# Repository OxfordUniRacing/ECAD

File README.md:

View this project on [CADLAB.io](https://cadlab.io/project/1514). 

# ECAD
Schematics and designs for the electronics team
See notes on project struture in the Oxford Uni Racing ECAD project description.
Built with EAGLE 9.2.2

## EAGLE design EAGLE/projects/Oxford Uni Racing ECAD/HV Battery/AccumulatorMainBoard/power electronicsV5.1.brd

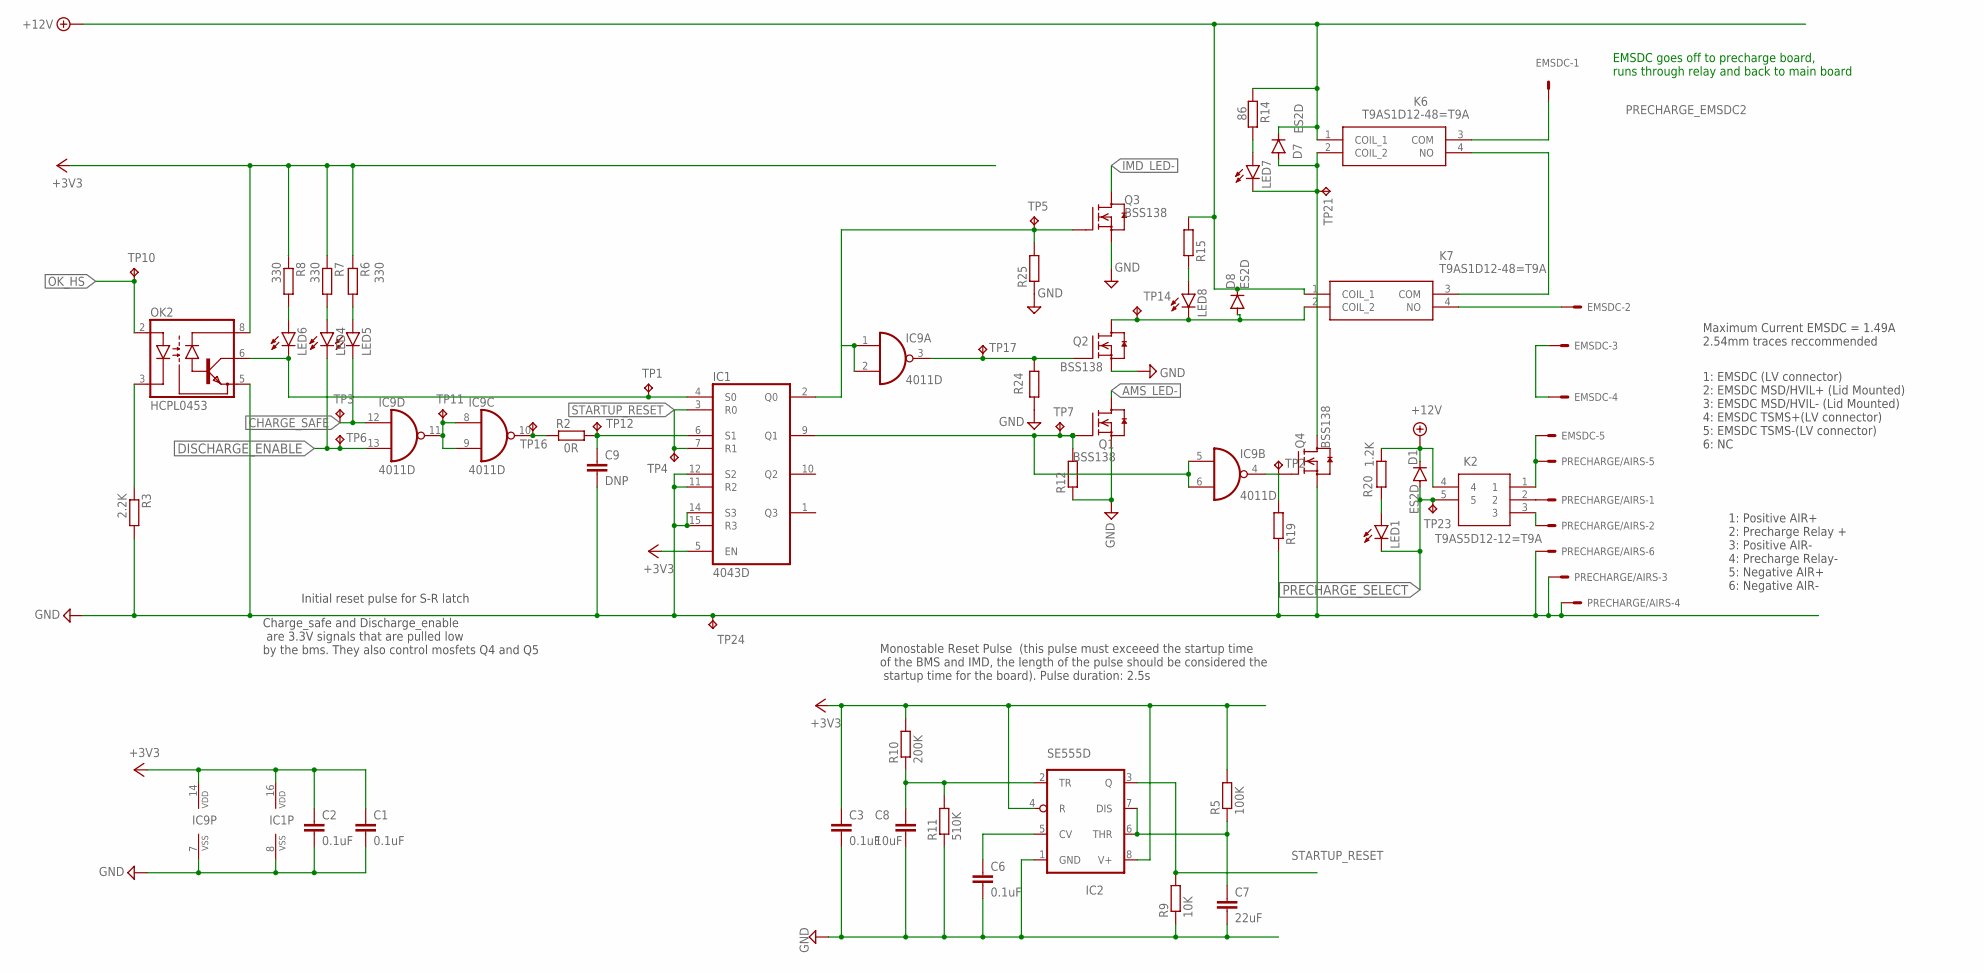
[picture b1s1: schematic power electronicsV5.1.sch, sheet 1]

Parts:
C1, C2, C3, C6: 0.1uF; C0805
C7: 22uF; C1206
C8: 10uF; C0805
C9: DNP; C0805K
D1, D7, D8: ES2D; SMB
EMSDC: KK-156-6
IC1: 4043D; SO16
IC2: SE555D; SO08
IC9: 4011D; SO14
K2: T9AS5D12-12=T9A; T9AS1D12
K6, K7: T9AS1D12-48=T9A; T9AS1D1248T9A
LED1, LED4, LED5, LED6, LED7, LED8: LEDSML0805; SML0805
OK2: HCPL0453; SOIC08
PRECHARGE/AIRS: KK-156-6
Q1, Q2, Q3, Q4: BSS138; SOT23
R2: 0R; R0805
R3: 2.2K; R0805
R5: 100K; R0805
R6, R7, R8: 330; R0805
R9: 10K; R0805
R10: 200K; R0805
R11: 510K; R0805
R12, R14, R15, R19, R24, R25: R-EU_R0805; R0805
R20: 1.2K; R0805
TP1, TP2, TP3, TP4, TP5, TP6, TP7, TP10, TP11, TP12, TP14, TP16, TP17, TP21, TP23, TP24: TPPAD1-17; P1-17

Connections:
+3V3: C1.1, C2.1, C3.1, IC1.5 (EN), IC1.16 (VDD), IC2.4 (R), IC2.8 (V+), IC9.14 (VDD), OK2.8 (VCC), R5.2, R6.1, R7.1, R8.1, R10.2
+12V: D1.C, D7.C, D8.C, K2.4, K6.1 (COIL_1), K7.1 (COIL_1), R14.2, R15.2, R20.1; also elsewhere on the board
AMS_LED-: Q1.3 (D); also elsewhere on the board
CHARGE_SAFE: IC9.12 (I0), LED5.C, TP3.TP; also elsewhere on the board
DISCHARGE_ENABLE: IC1.9 (Q1), IC9.5 (I0), IC9.6 (I1), IC9.13 (I1), LED4.C, Q1.1 (G), R12.2, TP6.TP, TP7.TP; also elsewhere on the board
GND: C1.2, C2.2, C3.2, C6.2, C7.2, C8.2, C9.2, IC1.8 (VSS), IC1.11 (R2), IC1.12 (S2), IC1.14 (S3), IC1.15 (R3), IC2.1 (GND), IC9.7 (VSS), OK2.5 (GND), PRECHARGE/AIRS.3, PRECHARGE/AIRS.4, PRECHARGE/AIRS.6, Q1.2 (S), Q2.2 (S), Q3.2 (S), Q4.2 (S), R3.2, R9.1, R11.1, R12.1, R19.1, R24.1, R25.1, TP24.TP; also elsewhere on the board
IMD_COIL_OUT: D8.A, K7.2 (COIL_2), LED8.C, Q2.3 (D), TP14.TP
IMD_LED-: Q3.3 (D); also elsewhere on the board
unnamed: IC9.10 (O), R2.1, TP16.TP
unnamed: K2.2, PRECHARGE/AIRS.1
unnamed: IC1.4 (S0), LED6.C, OK2.6 (VO), TP1.TP
unnamed: IC9.8 (I0), IC9.9 (I1), IC9.11 (O), TP11.TP
unnamed: OK2.3 (C), R3.1
unnamed: IC9.3 (O), Q2.1 (G), R24.2, TP17.TP
unnamed: IC1.2 (Q0), IC9.1 (I0), IC9.2 (I1), Q3.1 (G), R25.2, TP5.TP
unnamed: C9.1, IC1.6 (S1), R2.2, TP12.TP
unnamed: EMSDC.5, K2.1, PRECHARGE/AIRS.5
unnamed: K2.3, PRECHARGE/AIRS.2
unnamed: EMSDC.2, K7.4 (NO)
unnamed: D7.A, K6.2 (COIL_2), LED7.C, Q4.3 (D), TP21.TP
unnamed: IC9.4 (O), Q4.1 (G), R19.2, TP2.TP
unnamed: C7.1, IC2.6 (THR), IC2.7 (DIS), R5.1
unnamed: LED7.A, R14.1
unnamed: EMSDC.3, EMSDC.4
unnamed: LED8.A, R15.1
unnamed: K6.4 (NO), K7.3 (COM)
unnamed: LED1.A, R20.2
unnamed: LED4.A, R7.2
unnamed: LED5.A, R6.2
unnamed: LED6.A, R8.2
unnamed: C8.1, IC2.2 (TR), R10.1, R11.2
unnamed: C6.1, IC2.5 (CV)
OK_HS: OK2.2 (A), TP10.TP; also elsewhere on the board
PRECHARGE_EMSDC2: EMSDC.1, K6.3 (COM)
PRECHARGE_SELECT: D1.A, K2.5, LED1.C, TP23.TP; also elsewhere on the board
STARTUP_RESET: IC1.3 (R0), IC1.7 (R1), IC2.3 (Q), R9.2, TP4.TP

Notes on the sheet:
Initial reset pulse for S-R latch
1: EMSDC (LV connector) 2: EMSDC MSD/HVIL+ (Lid Mounted) 3: EMSDC MSD/HVIL- (Lid Mounted) 4: EMSDC TSMS+(LV connector) 5: EMSDC TSMS-(LV connector) 6: NC
1: Positive AIR+ 2: Precharge Relay + 3: Positive AIR- 4: Precharge Relay- 5: Negative AIR+ 6: Negative AIR-
Maximum Current EMSDC = 1.49A 2.54mm traces reccommended
Charge_safe and Discharge_enable are 3.3V signals that are pulled low by the bms. They also control mosfets Q4 and Q5
EMSDC goes off to precharge board, runs through relay and back to main board
Monostable Reset Pulse (this pulse must exceeed the startup time of the BMS and IMD, the length of the pulse should be considered the startup time for the board). Pulse duration: 2.5s

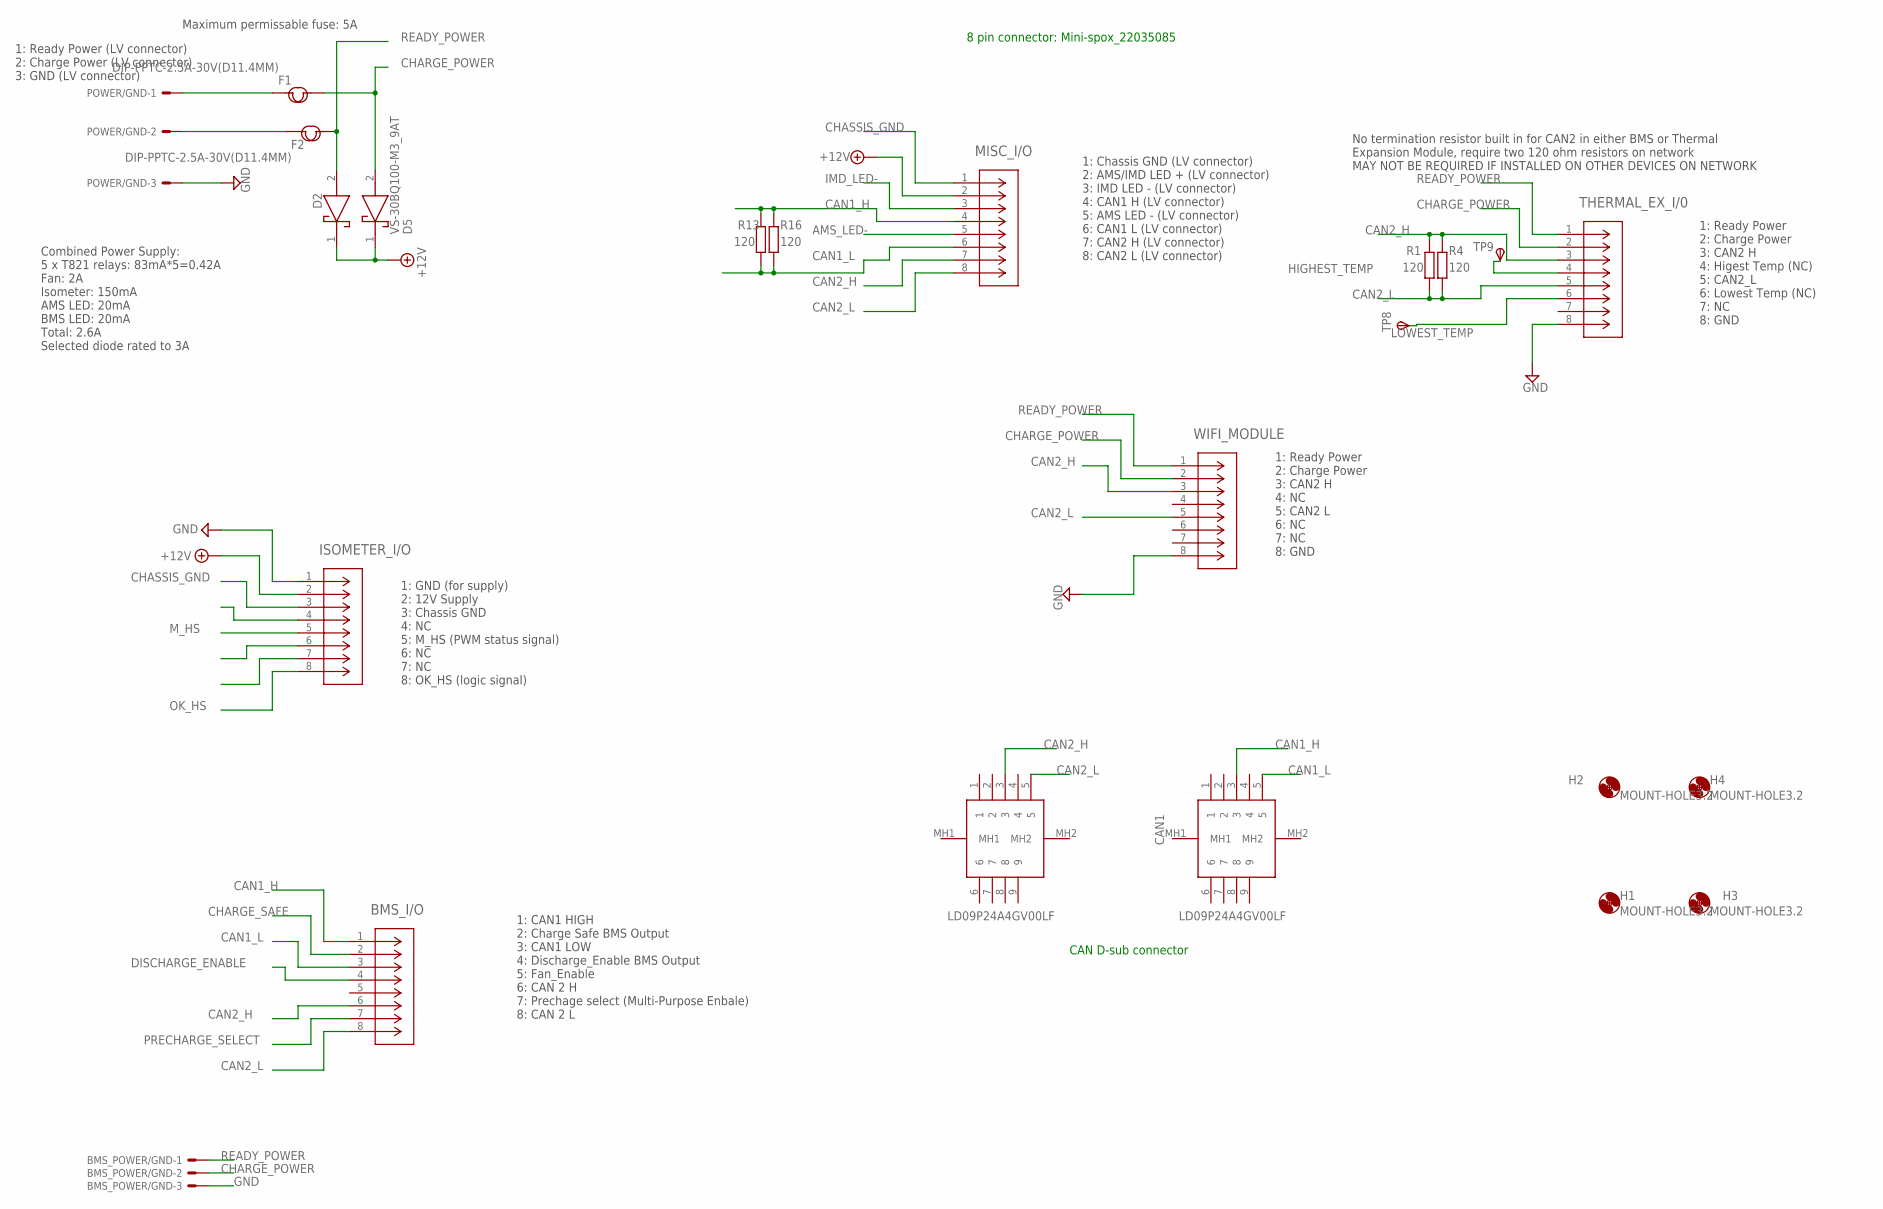
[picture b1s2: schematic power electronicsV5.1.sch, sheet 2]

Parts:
BMS_I/O: MINI-SPOX_22035085; CON_22035085_MOL
BMS_POWER/GND: KK-156-3
CAN1, CAN2: LD09P24A4GV00LF
D2, D5: VS-30BQ100-M3_9AT; DIOM7959X262N
F1, F2: DIP-PPTC-2.5A-30V(D11.4MM); F2-5.1-11.4X3.0X18.3MM
H1, H2, H3, H4: MOUNT-HOLE3.2; 3,2
ISOMETER_I/O: MINI-SPOX_22035085; CON_22035085_MOL
MISC_I/O: MINI-SPOX_22035085; CON_22035085_MOL
POWER/GND: KK-156-3
R1, R4, R13, R16: 120; R1206
THERMAL_EX_I/0: MINI-SPOX_22035085; CON_22035085_MOL
TP8, TP9: TPSTP11R; TP11R
WIFI_MODULE: MINI-SPOX_22035085; CON_22035085_MOL

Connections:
+12V: D2.1 (K), D5.1 (K), ISOMETER_I/O.2, MISC_I/O.2; also elsewhere on the board
AMS_LED-: MISC_I/O.5; also elsewhere on the board
CAN1_H: BMS_I/O.1, CAN1.3, MISC_I/O.4, R13.1, R16.1
CAN1_L: BMS_I/O.3, CAN1.5, MISC_I/O.6, R13.2, R16.2
CAN2_H: BMS_I/O.6, CAN2.3, MISC_I/O.7, R1.1, R4.1, THERMAL_EX_I/0.3, WIFI_MODULE.3
CAN2_L: BMS_I/O.8, CAN2.5, MISC_I/O.8, R1.2, R4.2, THERMAL_EX_I/0.5, WIFI_MODULE.5
CHARGE_POWER: BMS_POWER/GND.2, D5.2 (A), F1.1, THERMAL_EX_I/0.2, WIFI_MODULE.2
CHARGE_SAFE: BMS_I/O.2; also elsewhere on the board
CHASSIS_GND: ISOMETER_I/O.3, MISC_I/O.1
DISCHARGE_ENABLE: BMS_I/O.4; also elsewhere on the board
GND: BMS_POWER/GND.3, ISOMETER_I/O.1, POWER/GND.3, THERMAL_EX_I/0.8, WIFI_MODULE.8; also elsewhere on the board
HIGHEST_TEMP: THERMAL_EX_I/0.4, TP9.TP
IMD_LED-: MISC_I/O.3; also elsewhere on the board
LOWEST_TEMP: THERMAL_EX_I/0.6, TP8.TP
M_HS: ISOMETER_I/O.5
unnamed: F2.2, POWER/GND.2
unnamed: F1.2, POWER/GND.1
OK_HS: ISOMETER_I/O.8; also elsewhere on the board
PRECHARGE_SELECT: BMS_I/O.7; also elsewhere on the board
READY_POWER: BMS_POWER/GND.1, D2.2 (A), F2.1, THERMAL_EX_I/0.1, WIFI_MODULE.1

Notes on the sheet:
1: Chassis GND (LV connector) 2: AMS/IMD LED + (LV connector) 3: IMD LED - (LV connector) 4: CAN1 H (LV connector) 5: AMS LED - (LV connector) 6: CAN1 L (LV connector) 7: CAN2 H (LV connector) 8: CAN2 L (LV connector)
1: GND (for supply) 2: 12V Supply 3: Chassis GND 4: NC 5: M_HS (PWM status signal) 6: NC 7: NC 8: OK_HS (logic signal)
1: CAN1 HIGH 2: Charge Safe BMS Output 3: CAN1 LOW 4: Discharge_Enable BMS Output 5: Fan_Enable 6: CAN 2 H 7: Prechage select (Multi-Purpose Enbale) 8: CAN 2 L
Maximum permissable fuse: 5A
No termination resistor built in for CAN2 in either BMS or Thermal Expansion Module, require two 120 ohm resistors on network MAY NOT BE REQUIRED IF INSTALLED ON OTHER DEVICES ON NETWORK
1: Ready Power 2: Charge Power 3: CAN2 H 4: Higest Temp (NC) 5: CAN2_L 6: Lowest Temp (NC) 7: NC 8: GND
1: Ready Power 2: Charge Power 3: CAN2 H 4: NC 5: CAN2 L 6: NC 7: NC 8: GND
Combined Power Supply: 5 x T821 relays: 83mA*5=0.42A Fan: 2A Isometer: 150mA AMS LED: 20mA BMS LED: 20mA Total: 2.6A Selected diode rated to 3A
1: Ready Power (LV connector) 2: Charge Power (LV connector) 3: GND (LV connector)
CAN D-sub connector
8 pin connector: Mini-spox_22035085

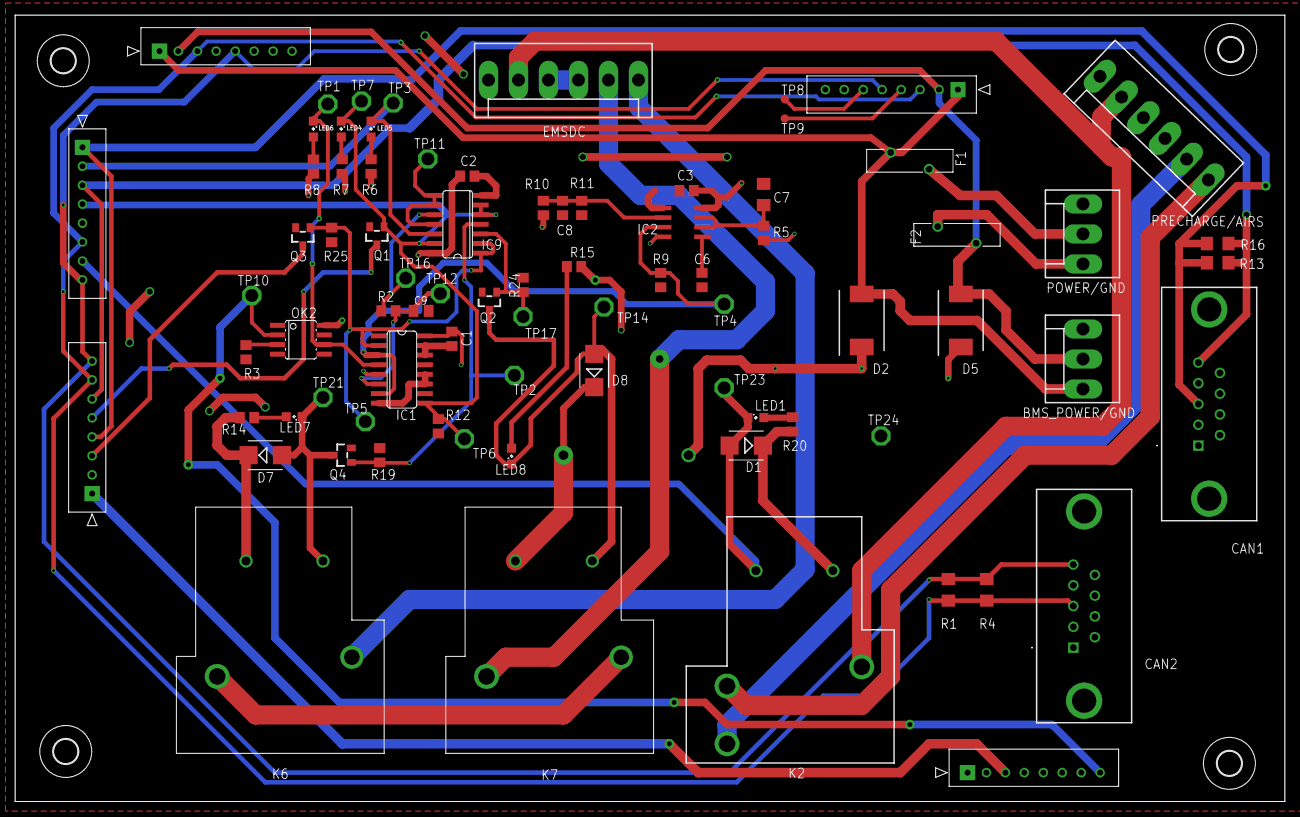
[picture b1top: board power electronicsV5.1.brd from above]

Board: 2 copper layers, 167.6 x 103.8 mm, 84 parts (0 on the bottom side), 47 nets.

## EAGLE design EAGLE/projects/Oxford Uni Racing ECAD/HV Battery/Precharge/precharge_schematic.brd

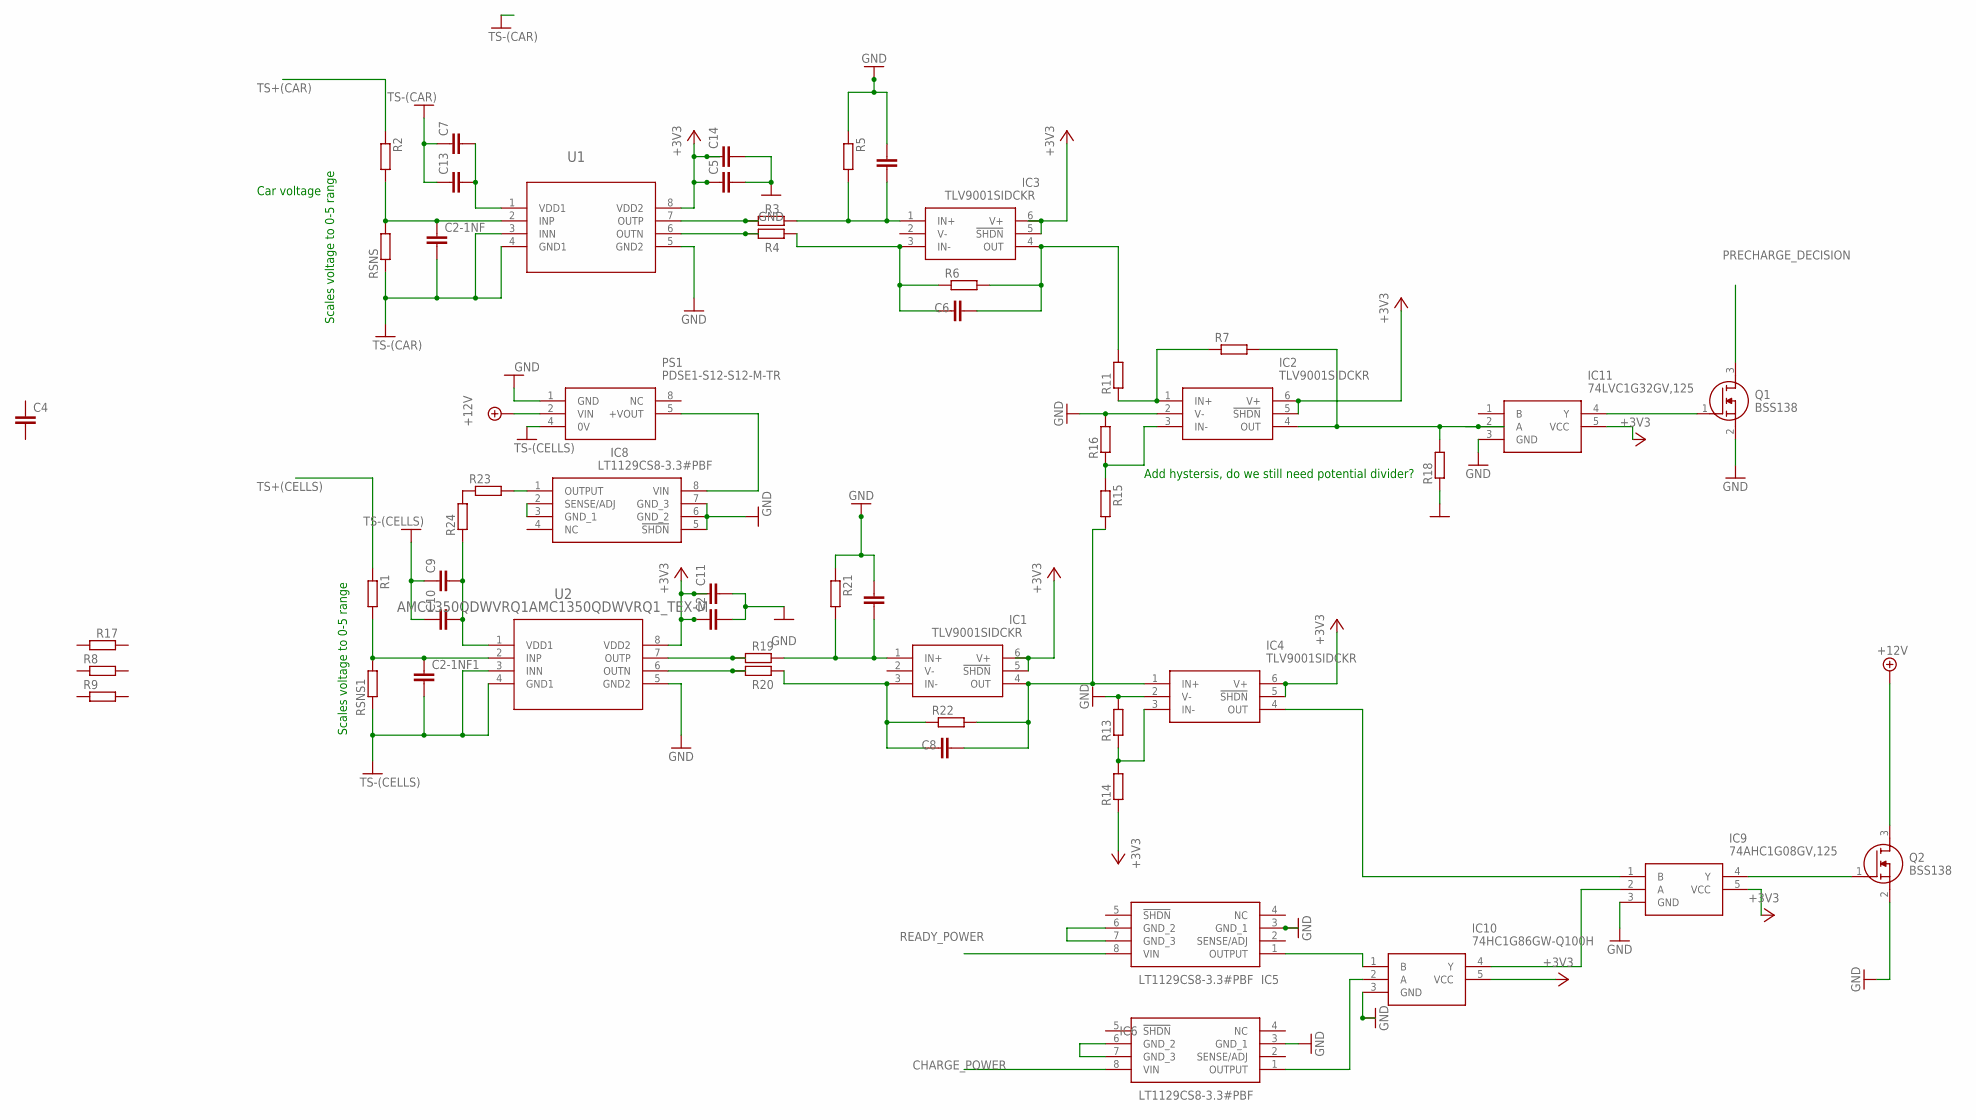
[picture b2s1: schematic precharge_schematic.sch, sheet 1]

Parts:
C1, C2, C2-1NF, C2-1NF1, C3, C4, C5, C6, C7, C8, C9, C10, C11, C13, C14: C-EUC0805; C0805
IC1, IC2, IC3, IC4: TLV9001SIDCKR; SOT65P210X110-6N
IC5, IC6, IC8: LT1129CS8-3.3#PBF; SOIC127P599X175-8N
IC9: 74AHC1G08GV,125; SOT95P275X110-5N
IC10: 74HC1G86GW-Q100H; SOT65P212X110-5N
IC11: 74LVC1G32GV,125; SOT95P275X110-5N
PS1: PDSE1-S12-S12-M-TR; PDSE1S12S12MTR
Q1, Q2: BSS138; SOT95P240X120-3N
R1, R2, R3, R4, R5, R6, R7, R8, R9, R11, R13, R14, R15, R16, R17, R18, R19, R20, R21, R22, R23, R24: R-EU_R0805; R0805
RSNS, RSNS1: R-EU_R0805; R0805
U1, U2: AMC1350QDWVRQ1AMC1350QDWVRQ1_TEX-M; AMC1350QDWVRQ1_TEX-M; MANUFACTURER_PART_NUMBER AMC1350

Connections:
3V3: C2.1, C5.1, C11.1, C14.1, IC1.5 (!SHDN), IC1.6 (V+), IC2.5 (!SHDN), IC2.6 (V+), IC3.5 (!SHDN), IC3.6 (V+), IC4.5 (!SHDN), IC4.6 (V+), IC9.5 (VCC), IC10.5 (VCC), IC11.5 (VCC), R14.1, U1.8 (VDD2), U2.8 (VDD2)
+12V: PS1.2 (VIN), Q2.3 (D)
CHARGE_POWER: IC6.8 (VIN)
GND: C1.1, C2.2, C3.1, C5.2, C11.2, C14.2, IC2.2 (V-), IC4.2 (V-), IC5.3 (GND_1), IC6.3 (GND_1), IC8.5 (!SHDN), IC8.6 (GND_2), IC8.7 (GND_3), IC9.3 (GND), IC10.3 (GND), IC11.3 (GND), PS1.1 (GND), Q1.2 (S), Q2.2 (S), R5.1, R13.2, R16.2, R18.1, R21.1, U1.5 (GND2), U2.5 (GND2)
GND(LV): C2-1NF.2, C2-1NF1.2, C7.1, C9.1, C10.1, C13.1, PS1.4 (0V), RSNS.1, RSNS1.1, U1.3 (INN), U1.4 (GND1), U2.3 (INN), U2.4 (GND1)
unnamed: C2-1NF.1, R2.2, RSNS.2, U1.2 (INP)
unnamed: C6.2, IC3.4 (OUT), R6.2, R11.2
unnamed: R4.1, U1.6 (OUTN)
unnamed: R3.1, U1.7 (OUTP)
unnamed: C2-1NF1.1, R1.2, RSNS1.2, U2.2 (INP)
unnamed: C3.2, IC3.1 (IN+), R3.2, R5.2
unnamed: C6.1, IC3.3 (IN-), R4.2, R6.1
unnamed: IC2.4 (OUT), IC11.2 (A), R7.2, R18.2
unnamed: R19.1, U2.7 (OUTP)
unnamed: R20.1, U2.6 (OUTN)
unnamed: C1.2, IC1.1 (IN+), R19.2, R21.2
unnamed: C8.1, IC1.3 (IN-), R20.2, R22.1
unnamed: IC8.2 (SENSE/ADJ), IC8.3 (GND_1)
unnamed: C8.2, IC1.4 (OUT), IC2.3 (IN-), IC4.1 (IN+), R15.1, R15.2, R16.1, R22.2
unnamed: IC4.3 (IN-), R13.1, R14.2
unnamed: IC2.1 (IN+), R7.1, R11.1
unnamed: IC4.4 (OUT), IC9.1 (B)
unnamed: IC8.8 (VIN), PS1.5 (+VOUT)
unnamed: R23.1, R24.2
unnamed: IC8.1 (OUTPUT), R23.2
unnamed: C9.2, C10.2, R24.1, U2.1 (VDD1)
unnamed: C7.2, C13.2, U1.1 (VDD1)
unnamed: IC6.1 (OUTPUT), IC10.2 (A)
unnamed: IC5.1 (OUTPUT), IC10.1 (B)
unnamed: IC9.2 (A), IC10.4 (Y)
unnamed: IC9.4 (Y), Q2.1 (G)
unnamed: IC6.6 (GND_2), IC6.7 (GND_3)
unnamed: IC5.6 (GND_2), IC5.7 (GND_3)
unnamed: IC11.4 (Y), Q1.1 (G)
PRECHARGE_DECISION: Q1.3 (D); also elsewhere on the board
READY_POWER: IC5.8 (VIN)
TS+(CAR): R2.1; also elsewhere on the board
TS+(CELLS): R1.1; also elsewhere on the board

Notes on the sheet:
Scales voltage to 0-5 range
Add hystersis, do we still need potential divider?
Car voltage

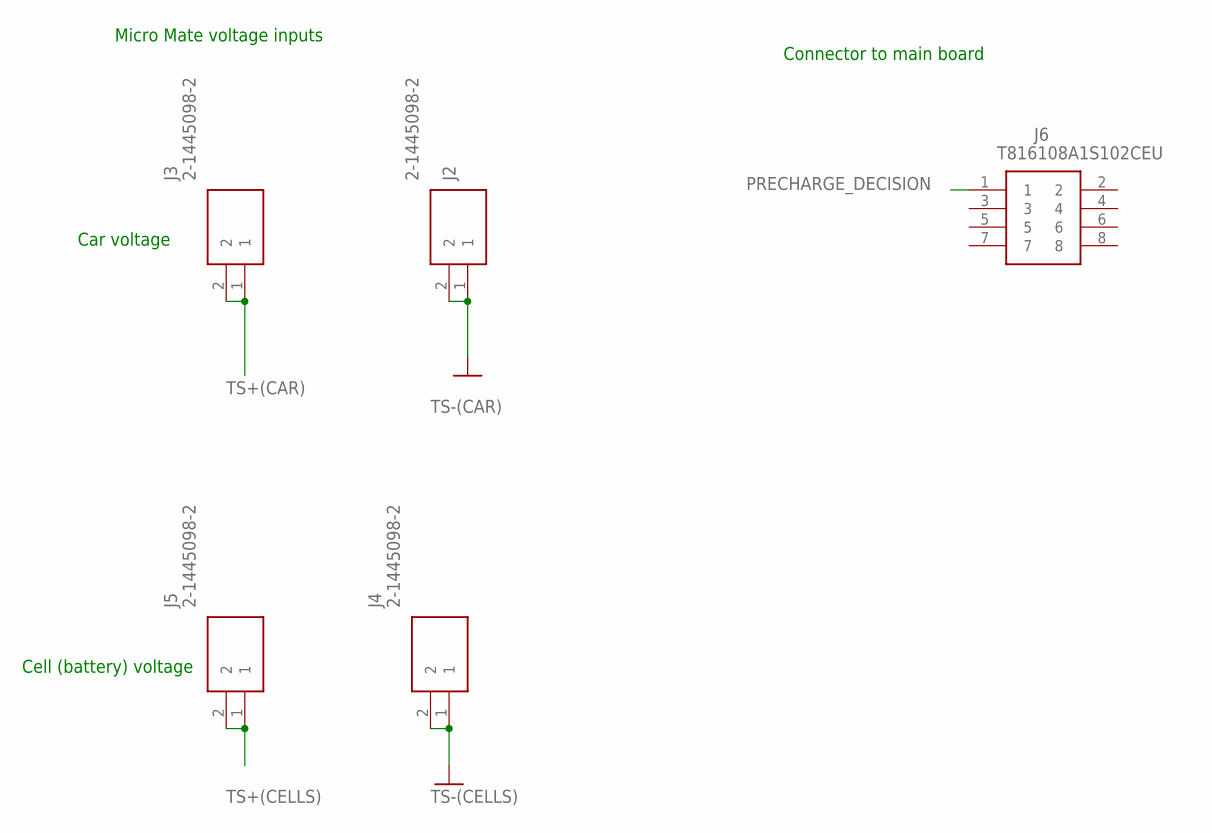
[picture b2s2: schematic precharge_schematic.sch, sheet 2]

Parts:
J2, J3, J4, J5: 2-1445098-2; 214450982
J6: T816108A1S102CEU

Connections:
unnamed: J2.1, J2.2
unnamed: J4.1, J4.2
PRECHARGE_DECISION: J6.1; also elsewhere on the board
TS+(CAR): J3.1, J3.2; also elsewhere on the board
TS+(CELLS): J5.1, J5.2; also elsewhere on the board

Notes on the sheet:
Car voltage
Cell (battery) voltage
Micro Mate voltage inputs
Connector to main board

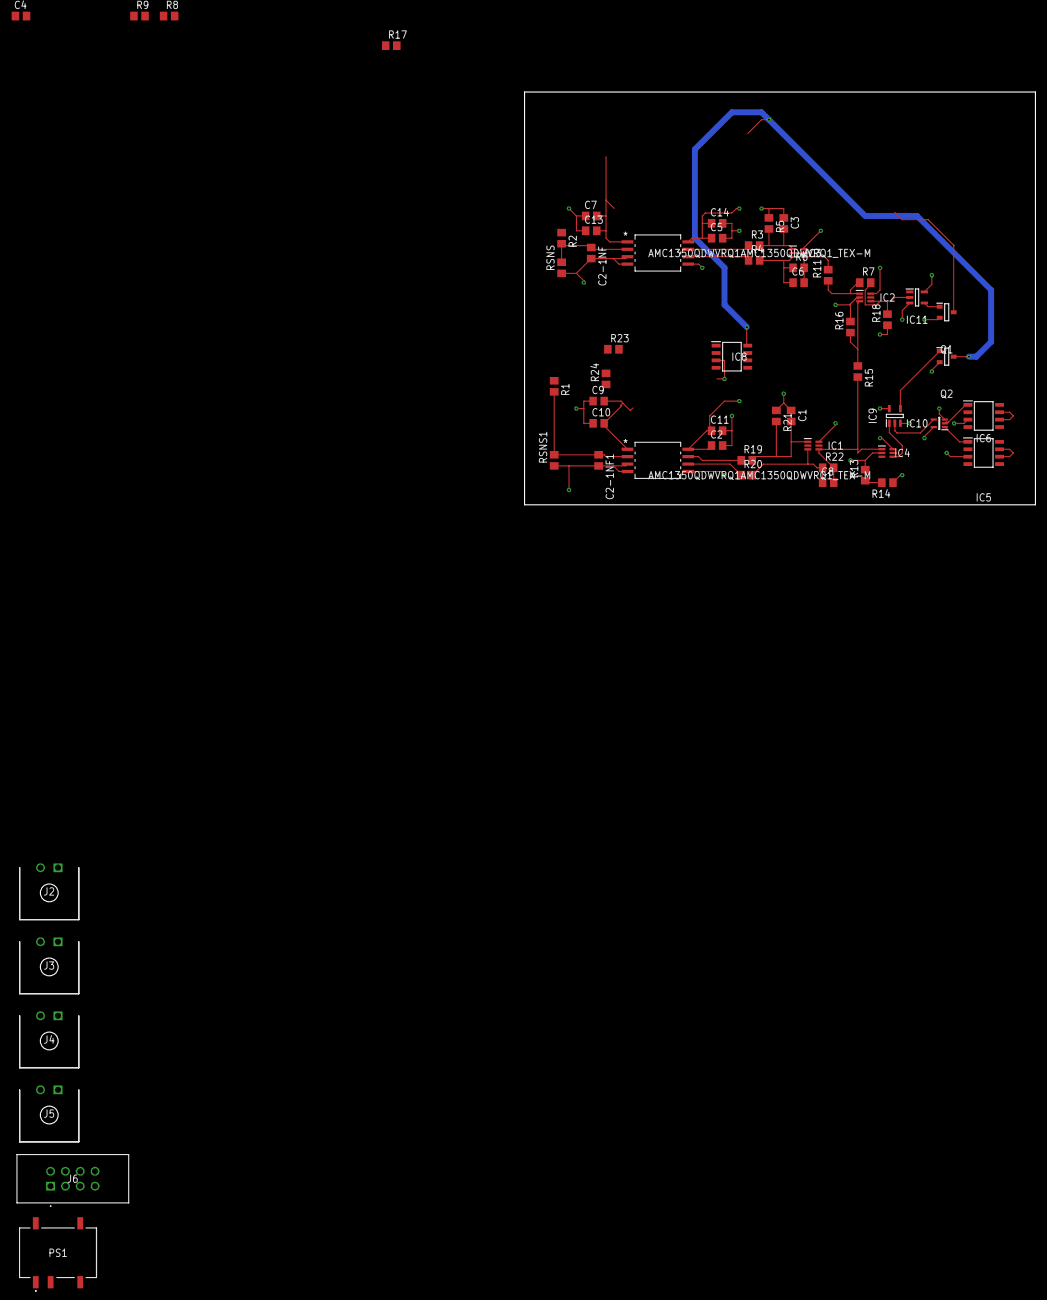
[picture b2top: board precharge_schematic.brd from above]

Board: 2 copper layers, 87.6 x 70.8 mm, 59 parts (0 on the bottom side), 38 nets.

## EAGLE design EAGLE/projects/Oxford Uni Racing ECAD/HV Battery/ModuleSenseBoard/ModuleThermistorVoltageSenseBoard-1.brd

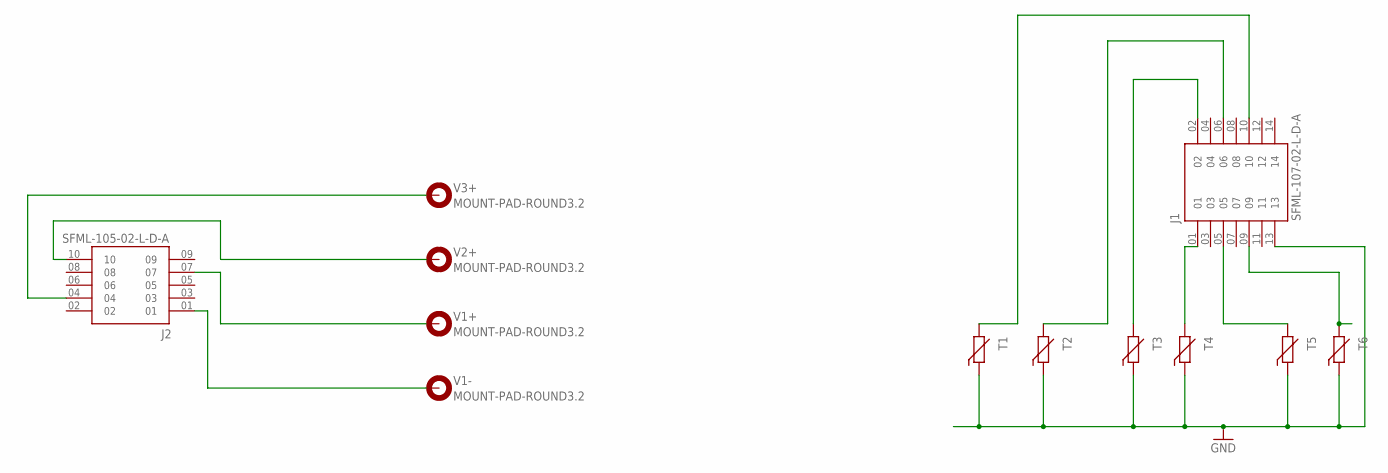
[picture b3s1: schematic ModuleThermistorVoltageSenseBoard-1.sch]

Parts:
J1: SFML-107-02-L-D-A; SAMTEC_SFML-107-02-L-D-A
J2: SFML-105-02-L-D-A; SAMTEC_SFML-105-02-L-D-A
T1, T2, T3, T4, T5, T6: THERMISTOR; THERMISTOR_CUTOUT
V1+, V1-, V2+, V3+: MOUNT-PAD-ROUND3.2; 3,2-PAD

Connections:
GND: J1.13, T1.1, T2.1, T3.1, T4.1, T5.1, T6.1
unnamed: J1.05, T5.2
unnamed: J1.09, T6.2
unnamed: J1.01, T4.2
unnamed: J1.02, T3.2
unnamed: J1.06, T2.2
unnamed: J1.10, T1.2
V1+: J2.07, V1+.B3,2
V1-: J2.01, V1-.B3,2
V2+: J2.10, V2+.B3,2
V3+: J2.04, V3+.B3,2

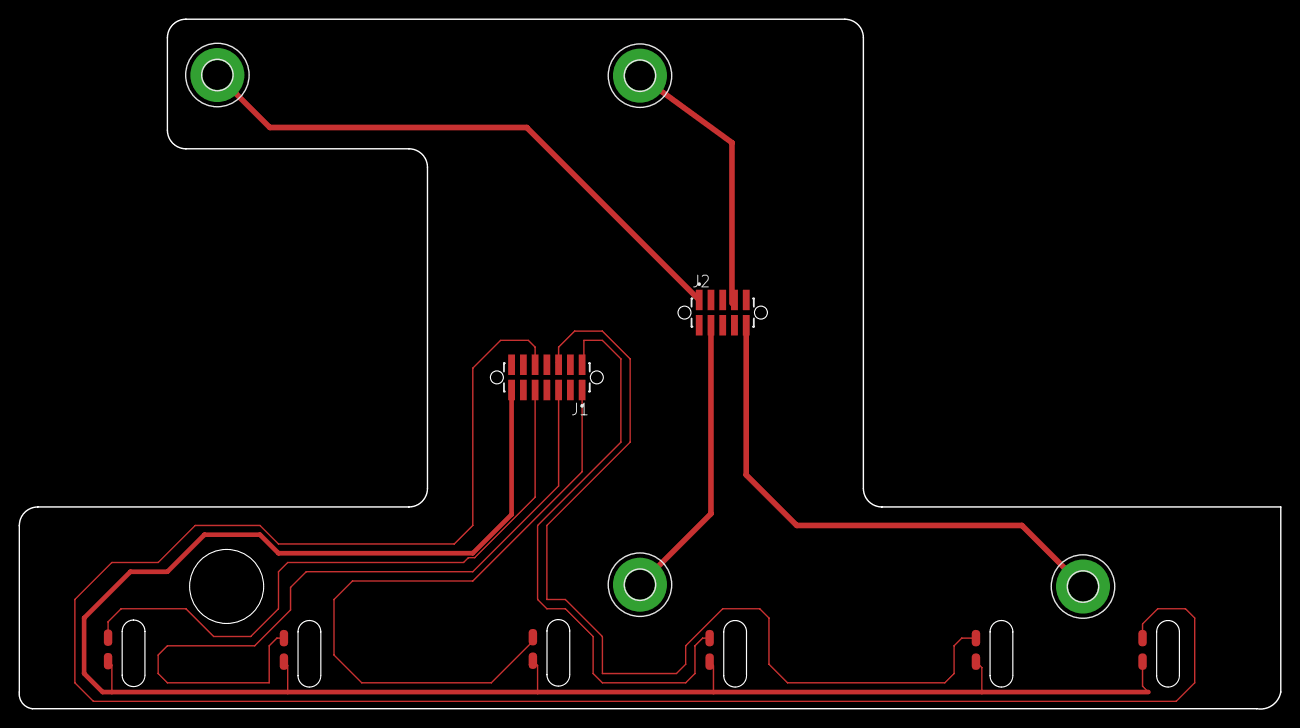
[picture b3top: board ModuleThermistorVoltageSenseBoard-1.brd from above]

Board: 2 copper layers, 136.3 x 74.5 mm, 12 parts (0 on the bottom side), 11 nets.

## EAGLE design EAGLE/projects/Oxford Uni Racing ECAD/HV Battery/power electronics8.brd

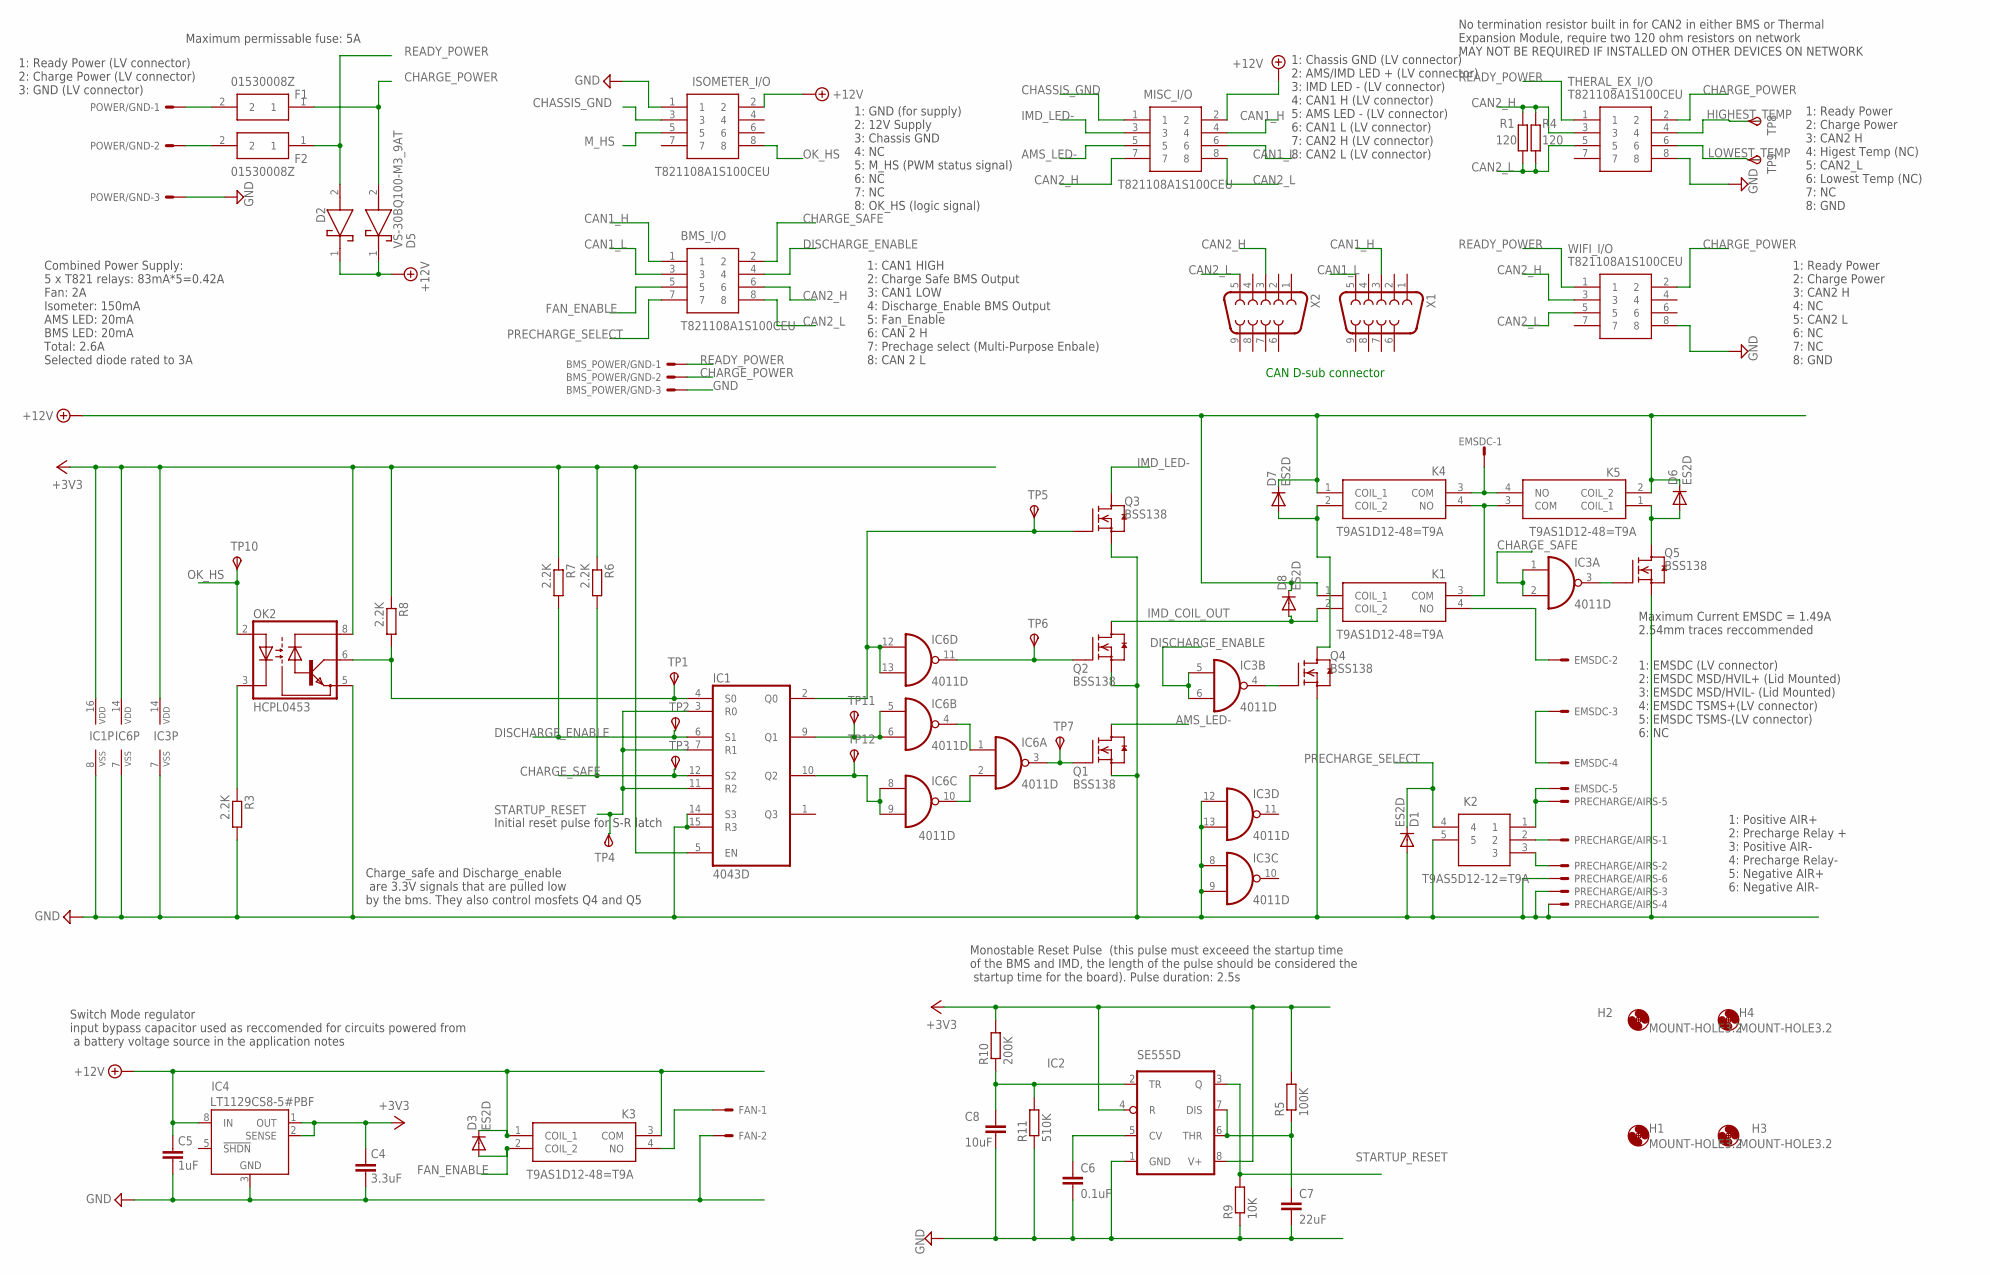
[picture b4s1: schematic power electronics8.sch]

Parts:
BMS_I/O: T821108A1S100CEU; HDRV8W64P254_2X4_1778X895X915P
BMS_POWER/GND: KK-156-3
C4: 3.3uF; C1206
C5: 1uF; C1206
C6: 0.1uF; C1206
C7: 22uF; C1206
C8: 10uF; C1206
D1, D3, D6, D7, D8: ES2D; SMB
D2, D5: VS-30BQ100-M3_9AT; DIOM7959X262N
EMSDC: KK-156-6
F1, F2: 01530008Z; 01530008
FAN: KK-156-2
H1, H2, H3, H4: MOUNT-HOLE3.2; 3,2
IC1: 4043D; SO16
IC2: SE555D; SO08
IC3, IC6: 4011D; SO14
IC4: LT1129CS8; SOIC8
ISOMETER_I/O: T821108A1S100CEU; HDRV8W64P254_2X4_1778X895X915P
K1, K3, K4, K5: T9AS1D12-48=T9A; T9AS1D1248T9A
K2: T9AS5D12-12=T9A; T9AS1D12
MISC_I/O: T821108A1S100CEU; HDRV8W64P254_2X4_1778X895X915P
OK2: HCPL0453; SOIC08
POWER/GND: KK-156-3
PRECHARGE/AIRS: KK-156-6
Q1, Q2, Q3, Q4, Q5: BSS138; SOT23
R1, R4: 120; R1206
R3, R6, R7, R8: 2.2K; R1206
R5: 100K; R1206
R9: 10K; R1206
R10: 200K; R1206
R11: 510K; R1206
THERAL_EX_I/O: T821108A1S100CEU; HDRV8W64P254_2X4_1778X895X915P
TP1, TP2, TP3, TP4, TP5, TP6, TP7, TP8, TP9, TP10, TP11, TP12: TPSTP11R; TP11R
WIFI_I/O: T821108A1S100CEU; HDRV8W64P254_2X4_1778X895X915P
X1, X2: F09V

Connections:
+3V3: C4.1, IC1.5 (EN), IC1.16 (VDD), IC2.4 (R), IC2.8 (V+), IC3.14 (VDD), IC4.1 (OUT), IC4.2 (SENSE), IC6.14 (VDD), OK2.8 (VCC), R5.2, R6.1, R7.1, R8.1, R10.2
+12V: C5.1, D2.1 (K), D3.C, D5.1 (K), D6.C, D7.C, D8.C, IC4.8 (IN), ISOMETER_I/O.2, K1.1 (COIL_1), K3.1 (COIL_1), K3.3 (COM), K4.1 (COIL_1), K5.2 (COIL_2), MISC_I/O.2
AMS_LED-: MISC_I/O.5, Q1.3 (D)
CAN1_H: BMS_I/O.1, MISC_I/O.4, X1.3
CAN1_L: BMS_I/O.3, MISC_I/O.6, X1.5
CAN2_H: BMS_I/O.6, MISC_I/O.7, R1.1, R4.1, THERAL_EX_I/O.3, WIFI_I/O.3, X2.3
CAN2_L: BMS_I/O.8, MISC_I/O.8, R1.2, R4.2, THERAL_EX_I/O.5, WIFI_I/O.5, X2.5
CHARGE_POWER: BMS_POWER/GND.2, D5.2 (A), F1.1, THERAL_EX_I/O.2, WIFI_I/O.2
CHARGE_SAFE: BMS_I/O.2, IC1.12 (S2), IC3.1 (I0), IC3.2 (I1), R6.2, TP3.TP
CHASSIS_GND: ISOMETER_I/O.3, MISC_I/O.1
DISCHARGE_ENABLE: BMS_I/O.4, IC1.6 (S1), IC3.5 (I0), IC3.6 (I1), R7.2, TP2.TP
EMSDC_IMD+: K1.3 (COM), K4.4 (NO), K5.3 (COM)
FAN+: FAN.1, K3.4 (NO)
FAN_ENABLE: BMS_I/O.5, D3.A, K3.2 (COIL_2)
GND: BMS_POWER/GND.3, C4.2, C5.2, C6.2, C7.2, C8.2, D1.A, FAN.2, IC1.8 (VSS), IC1.14 (S3), IC1.15 (R3), IC2.1 (GND), IC3.7 (VSS), IC3.8 (I0), IC3.9 (I1), IC3.12 (I0), IC3.13 (I1), IC4.3 (GND), IC4.6 (GND), IC4.7 (GND), IC6.7 (VSS), ISOMETER_I/O.1, K2.5, OK2.5 (GND), POWER/GND.3, PRECHARGE/AIRS.3, PRECHARGE/AIRS.4, PRECHARGE/AIRS.6, Q1.2 (S), Q2.2 (S), Q3.2 (S), Q4.2 (S), Q5.2 (S), R3.2, R9.1, R11.1, THERAL_EX_I/O.8, WIFI_I/O.8
HIGHEST_TEMP: THERAL_EX_I/O.4, TP8.TP
IMD_COIL_OUT: D8.A, K1.2 (COIL_2), Q2.3 (D)
IMD_LED-: MISC_I/O.3, Q3.3 (D)
LOWEST_TEMP: THERAL_EX_I/O.6, TP9.TP
M_HS: ISOMETER_I/O.5
unnamed: EMSDC.1, K4.3 (COM), K5.4 (NO)
unnamed: F2.2, POWER/GND.2
unnamed: K2.2, PRECHARGE/AIRS.1
unnamed: F1.2, POWER/GND.1
unnamed: IC1.4 (S0), OK2.6 (VO), R8.2, TP1.TP
unnamed: D7.A, K4.2 (COIL_2), Q4.3 (D)
unnamed: OK2.3 (C), R3.1
unnamed: IC1.2 (Q0), IC6.12 (I0), IC6.13 (I1), Q3.1 (G), TP5.TP
unnamed: D6.A, K5.1 (COIL_1), Q5.3 (D)
unnamed: IC1.9 (Q1), IC6.5 (I0), IC6.6 (I1), TP11.TP
unnamed: EMSDC.5, K2.1, PRECHARGE/AIRS.5
unnamed: K2.3, PRECHARGE/AIRS.2
unnamed: IC1.10 (Q2), IC6.8 (I0), IC6.9 (I1), TP12.TP
unnamed: IC6.1 (I0), IC6.4 (O)
unnamed: EMSDC.2, K1.4 (NO)
unnamed: IC3.4 (O), Q4.1 (G)
unnamed: C7.1, IC2.6 (THR), IC2.7 (DIS), R5.1
unnamed: IC3.3 (O), Q5.1 (G)
unnamed: EMSDC.3, EMSDC.4
unnamed: IC6.2 (I1), IC6.10 (O)
unnamed: IC6.3 (O), Q1.1 (G), TP7.TP
unnamed: C8.1, IC2.2 (TR), R10.1, R11.2
unnamed: C6.1, IC2.5 (CV)
unnamed: IC6.11 (O), Q2.1 (G), TP6.TP
OK_HS: ISOMETER_I/O.8, OK2.2 (A), TP10.TP
PRECHARGE_SELECT: BMS_I/O.7, D1.C, K2.4
READY_POWER: BMS_POWER/GND.1, D2.2 (A), F2.1, THERAL_EX_I/O.1, WIFI_I/O.1
STARTUP_RESET: IC1.3 (R0), IC1.7 (R1), IC1.11 (R2), IC2.3 (Q), R9.2, TP4.TP

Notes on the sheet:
Initial reset pulse for S-R latch
Monostable Reset Pulse (this pulse must exceeed the startup time of the BMS and IMD, the length of the pulse should be considered the startup time for the board). Pulse duration: 2.5s
Switch Mode regulator input bypass capacitor used as reccomended for circuits powered from a battery voltage source in the application notes
1: Chassis GND (LV connector) 2: AMS/IMD LED + (LV connector) 3: IMD LED - (LV connector) 4: CAN1 H (LV connector) 5: AMS LED - (LV connector) 6: CAN1 L (LV connector) 7: CAN2 H (LV connector) 8: CAN2 L (LV connector)
1: GND (for supply) 2: 12V Supply 3: Chassis GND 4: NC 5: M_HS (PWM status signal) 6: NC 7: NC 8: OK_HS (logic signal)
1: CAN1 HIGH 2: Charge Safe BMS Output 3: CAN1 LOW 4: Discharge_Enable BMS Output 5: Fan_Enable 6: CAN 2 H 7: Prechage select (Multi-Purpose Enbale) 8: CAN 2 L
Maximum permissable fuse: 5A
No termination resistor built in for CAN2 in either BMS or Thermal Expansion Module, require two 120 ohm resistors on network MAY NOT BE REQUIRED IF INSTALLED ON OTHER DEVICES ON NETWORK
1: Ready Power 2: Charge Power 3: CAN2 H 4: Higest Temp (NC) 5: CAN2_L 6: Lowest Temp (NC) 7: NC 8: GND
1: Ready Power 2: Charge Power 3: CAN2 H 4: NC 5: CAN2 L 6: NC 7: NC 8: GND
Combined Power Supply: 5 x T821 relays: 83mA*5=0.42A Fan: 2A Isometer: 150mA AMS LED: 20mA BMS LED: 20mA Total: 2.6A Selected diode rated to 3A
1: EMSDC (LV connector) 2: EMSDC MSD/HVIL+ (Lid Mounted) 3: EMSDC MSD/HVIL- (Lid Mounted) 4: EMSDC TSMS+(LV connector) 5: EMSDC TSMS-(LV connector) 6: NC
1: Positive AIR+ 2: Precharge Relay + 3: Positive AIR- 4: Precharge Relay- 5: Negative AIR+ 6: Negative AIR-
1: Ready Power (LV connector) 2: Charge Power (LV connector) 3: GND (LV connector)
Maximum Current EMSDC = 1.49A 2.54mm traces reccommended
CAN D-sub connector
Charge_safe and Discharge_enable are 3.3V signals that are pulled low by the bms. They also control mosfets Q4 and Q5

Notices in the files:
parts and their libraries:
m-pad-2.1: License : GNU General Public License version 2 (see bottom)
COPYRIGHT: Copyright (C) 2023 Ultra Librarian. All rights reserved.
COPYRIGHT: Copyright (C) 2022 Ultra Librarian. All rights reserved.
